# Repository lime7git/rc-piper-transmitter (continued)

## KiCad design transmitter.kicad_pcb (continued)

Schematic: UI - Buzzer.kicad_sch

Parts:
BZ1: Buzzer; Buzzer_TDK_PS1240P02BT_D12.2mm_H6.5mm
D2: 1N5819WS; D_SOD-323
JP7: SolderJumper_3_Bridged12; SolderJumper-3_P2.0mm_Open_TrianglePad1.0x1.5mm_NumberLabels
Q4: AO3400A; SOT-23
R75: 330Ω; R_0402_1005Metric
R76: 47kΩ; R_0402_1005Metric

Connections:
+3.3V: JP7.3 (B); also elsewhere on the board
+5V: JP7.1 (A); also elsewhere on the board
/Project Architecture/MCU - IO/BUZZER: R75.1; also elsewhere on the board
GND: Q4.2 (S), R76.2; also elsewhere on the board
unnamed: BZ1.1 (+), D2.1 (K), JP7.2 (C)
unnamed: BZ1.2 (-), D2.2 (A), Q4.3 (D)
unnamed: Q4.1 (G), R75.2, R76.1

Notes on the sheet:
[${#}] ${TITLE}
Incremental rotary encoder with switch

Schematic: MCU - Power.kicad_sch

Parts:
C55, C56, C57, C58, C59, C60, C61, C62, C63, C64, C65, C69, C70, C74, C75: 100nF; C_0402_1005Metric
C66, C67, C68: 1uF; C_0603_1608Metric
C71: 4.7uF; C_0805_2012Metric
C72, C73: 2.2uF; C_1206_3216Metric
J3: B2B-PH-K-S; JST_PH_B2B-PH-K_1x02_P2.00mm_Vertical; not fitted
JP3: NO; SolderJumper-2_P1.3mm_Open_TrianglePad1.0x1.5mm
JP5, JP6: NC; SolderJumper-2_P1.3mm_Open_TrianglePad1.0x1.5mm
R61, R68, R95: 0Ω; R_0402_1005Metric
U1: STM32H743ZIT6TR; LQFP-144_1_STM

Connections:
+3.3V: C55.1, C56.1, C57.1, C58.1, C59.1, C60.1, C61.1, C62.1, C63.1, C64.1, C65.1, C71.1, C74.1, JP5.2 (B), JP6.1 (A), R61.1, U1.17 (VDD), U1.30 (VDD), U1.39 (VDD), U1.52 (VDD), U1.62 (VDD), U1.72 (VDD), U1.84 (VDD), U1.108 (VDD), U1.121 (VDD), U1.131 (VDD), U1.144 (VDD); also elsewhere on the board
GND: C55.2, C56.2, C57.2, C58.2, C59.2, C60.2, C61.2, C62.2, C63.2, C64.2, C65.2, C66.2, C71.2, C72.2, C73.2, C74.2, C75.2, J3.2, R95.2, U1.16 (VSS), U1.38 (VSS), U1.51 (VSS), U1.61 (VSS), U1.83 (VSS), U1.94 (VSS), U1.107 (VSS), U1.120 (VSS), U1.130 (VSS); also elsewhere on the board
GNDA: C67.2, C68.2, C69.2, C70.2, R95.1, U1.31 (VSSA)
unnamed: J3.1, JP3.1 (A)
unnamed: JP5.1 (A), U1.95 (VDD33USB)
VBAT: C66.1, JP3.2 (B), JP6.2 (B), U1.6 (VBAT)
VCAP: C72.1, C73.1, U1.71 (VCAP), U1.106 (VCAP)
VDDA: C68.1, C70.1, C75.1, R61.2, R68.2, U1.33 (VDDA)
VREF: C67.1, C69.1, R68.1, U1.32 (VREF+)

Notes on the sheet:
VBAT power domain
Analog decoupling
VCAP decoupling
[${#}] ${TITLE}
Microcontroller power decoupling
Microcontroller power
LAYOUT NOTE: Place each capacitor close to the relevant pin.

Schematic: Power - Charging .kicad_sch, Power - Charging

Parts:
C37, C39: 4.7uF; C_0805_2012Metric
C38, C41: 100nF; C_0402_1005Metric
C42: 10uF; C_0805_2012Metric
JP9, JP10: NO; SolderJumper-2_P1.3mm_Open_TrianglePad1.0x1.5mm
R47, R48: 10kΩ; R_0402_1005Metric
R49: 300kΩ; R_0603_1608Metric
R50: 0Ω; R_0402_1005Metric; not fitted
R96, R97: 0Ω; R_0402_1005Metric
U3: MP2667GG-0000-Z; QFN-10_2MMx2MM_MNP-L

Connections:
+3.3V: R49.1; also elsewhere on the board
+BATT: C42.1, JP10.1 (A), U3.8 (BATT), U3.9 (BATT); also elsewhere on the board
/Project Architecture/Auxiliary/I2C3_SCL: U3.6 (SCL); also elsewhere on the board
/Project Architecture/Auxiliary/I2C3_SDA: U3.7 (SDA); also elsewhere on the board
/Project Architecture/MCU - IO/CHARGER_INT: R49.2, U3.3 (INT); also elsewhere on the board
/Project Architecture/Power - Battery/NTC_BATT: R50.1; also elsewhere on the board
GND: C37.2, C38.2, C39.2, C41.2, C42.2, R47.2, U3.5 (GND); also elsewhere on the board
unnamed: R97.2, U3.1 (IN)
unnamed: R47.1, R48.2, R50.2, U3.2 (NTC)
unnamed: R96.1, U3.10 (SYS)
unnamed: C38.1, U3.4 (VDD)
VBUS: C37.1, JP9.1 (A), R48.1, R97.1; also elsewhere on the board
VSYS: C39.1, C41.1, JP9.2 (B), JP10.2 (B), R96.2; also elsewhere on the board

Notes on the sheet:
[${#}] ${TITLE}
Li-pol single-cell battery charger with Ppower path managment
DESIGN NOTE: Check for I2C addresses collisions

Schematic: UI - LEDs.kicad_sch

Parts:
D4: RED; LED_0603_1608Metric
D5: WHITE; LED_0603_1608Metric
R77, R78: 1kΩ; R_0402_1005Metric

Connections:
+3.3V: R77.1; also elsewhere on the board
/Project Architecture/MCU - IO/LED: D4.1 (K), D5.2 (A); also elsewhere on the board
GND: R78.1; also elsewhere on the board
unnamed: D4.2 (A), R77.2
unnamed: D5.1 (K), R78.2

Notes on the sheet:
LEDs
[${#}] ${TITLE}

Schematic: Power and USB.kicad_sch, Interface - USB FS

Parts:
C40: 10uF; C_0805_2012Metric
C43: 100nF; C_0402_1005Metric
IC4: USBLC6-2SC6; SOT95P280X145-6N; Manufacturer_Part_Number USBLC6-2SC6
J6: USB4085-GF-A; GCT_USB4085-GF-A_REVB
R51, R52: 5.1kΩ; R_0402_1005Metric

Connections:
/Project Architecture/Interface - USB FS/DN: IC4.1 (I/O1_1), J6.A7 (D-), J6.B7 (D-)
/Project Architecture/Interface - USB FS/DP: IC4.3 (I/O2_1), J6.A6 (D+), J6.B6 (D+)
/Project Architecture/Interface - USB FS/USB_OTG_FS_DN: IC4.6 (I/O1_2); also elsewhere on the board
/Project Architecture/Interface - USB FS/USB_OTG_FS_DP: IC4.4 (I/O2_2); also elsewhere on the board
GND: C40.2, C43.2, IC4.2 (GND), J6.A1 (GND), J6.A12 (GND), J6.B1 (GND), J6.B12 (GND), J6.S1 (SHIELD), R51.2, R52.2; also elsewhere on the board
unnamed: J6.A5 (CC1), R52.1
unnamed: J6.B5 (CC2), R51.1
VBUS: C40.1, C43.1, IC4.5 (VBUS), J6.A4 (VBUS), J6.A9 (VBUS), J6.B4 (VBUS), J6.B9 (VBUS); also elsewhere on the board

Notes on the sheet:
USB C
[${#}] ${TITLE}

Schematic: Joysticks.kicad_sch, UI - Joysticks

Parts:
C23, C24, C25, C26: 100nF; C_0402_1005Metric
R16, R17, R18, R19: 0Ω; R_0402_1005Metric
RV1: LeftX; JST_PH_B3B-PH-K_1x03_P2.00mm_Vertical
RV2: LeftY; JST_PH_B3B-PH-K_1x03_P2.00mm_Vertical
RV3: RightX; JST_PH_B3B-PH-K_1x03_P2.00mm_Vertical
RV4: RightY; JST_PH_B3B-PH-K_1x03_P2.00mm_Vertical

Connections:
+3.3V: RV1.1, RV2.1, RV3.1, RV4.1; also elsewhere on the board
/Project Architecture/MCU - IO/ADC1_INP4: C23.1, R16.1; also elsewhere on the board
/Project Architecture/MCU - IO/ADC1_INP7: C24.1, R17.1; also elsewhere on the board
/Project Architecture/MCU - IO/ADC1_INP8: C25.1, R18.1; also elsewhere on the board
/Project Architecture/MCU - IO/ADC1_INP16: C26.1, R19.1; also elsewhere on the board
/Project Architecture/UI - Joysticks/LX: R16.2, RV1.2
/Project Architecture/UI - Joysticks/LY: R17.2, RV2.2
/Project Architecture/UI - Joysticks/RX: R18.2, RV3.2
/Project Architecture/UI - Joysticks/RY: R19.2, RV4.2
GND: C23.2, C24.2, C25.2, C26.2, RV1.3, RV2.3, RV3.3, RV4.3; also elsewhere on the board

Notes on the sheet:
Right axis - 5kOhm potentiometers x2
DESIGN NOTE: Each axis input is connected via JST PHR 3pin header. 1 - 3.3V 2 - INPUT 3 - GND
[${#}] ${TITLE}

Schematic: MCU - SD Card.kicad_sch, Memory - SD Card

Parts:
CARD1: TF-SMD_TF-PUSH; Manufacturer Part TF PUSH
R40, R41, R42, R43, R44, R46: 47kΩ; R_0402_1005Metric
R45: 0Ω; R_0402_1005Metric

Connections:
+3.3V: CARD1.4 (VDD), R40.1, R41.1, R42.1, R43.1, R44.1, R46.1; also elsewhere on the board
/Project Architecture/MCU - IO/CD: R45.1; also elsewhere on the board
/Project Architecture/MCU - IO/SDMMC2_CK: CARD1.5 (CLK); also elsewhere on the board
/Project Architecture/MCU - IO/SDMMC2_CMD: CARD1.3 (CMD), R44.2; also elsewhere on the board
/Project Architecture/MCU - IO/SDMMC2_D0: CARD1.7 (DAT0), R43.2; also elsewhere on the board
/Project Architecture/MCU - IO/SDMMC2_D1: CARD1.8 (DAT1), R42.2; also elsewhere on the board
/Project Architecture/MCU - IO/SDMMC2_D2: CARD1.1 (DAT2), R41.2; also elsewhere on the board
/Project Architecture/MCU - IO/SDMMC2_D3: CARD1.2 (CD/DAT3), R40.2; also elsewhere on the board
GND: CARD1.6 (VSS); also elsewhere on the board
unnamed: CARD1.CD, R45.2, R46.2

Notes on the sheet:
[${#}] ${TITLE}
SD Card
DESIGN NOTE: Matched length on SDMMC2 net. [2.54mm tolerance]

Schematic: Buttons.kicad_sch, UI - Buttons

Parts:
C27, C28, C29, C30, C31, C32, C33, C34: 100nF; C_0402_1005Metric
D6, D7, D8, D9, D10, D11, D12, D13: ESD5Z5V0; D_SOD-523; not fitted
R20, R23, R25, R27, R29, R31, R33, R35: 47kΩ; R_0402_1005Metric
R21, R22, R24, R26, R28, R30, R32, R34: 5.1kΩ; R_0402_1005Metric
SW1, SW2, SW3, SW4, SW5, SW6, SW10, SW11: Button SPST SMD Tactile Switch; JST_PH_B2B-PH-K_1x02_P2.00mm_Vertical

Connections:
+3.3V: R20.1, R23.1, R25.1, R27.1, R29.1, R31.1, R33.1, R35.1; also elsewhere on the board
/Project Architecture/Auxiliary/BUTTON0: R21.1; also elsewhere on the board
/Project Architecture/Auxiliary/BUTTON1: R22.1; also elsewhere on the board
/Project Architecture/Auxiliary/BUTTON2: R24.1; also elsewhere on the board
/Project Architecture/Auxiliary/BUTTON3: R26.1; also elsewhere on the board
/Project Architecture/Auxiliary/BUTTON4: R28.1; also elsewhere on the board
/Project Architecture/Auxiliary/BUTTON5: R30.1; also elsewhere on the board
/Project Architecture/Auxiliary/BUTTON6: R32.1; also elsewhere on the board
/Project Architecture/Auxiliary/BUTTON7: R34.1; also elsewhere on the board
GND: C27.2, C28.2, C29.2, C30.2, C31.2, C32.2, C33.2, C34.2, D6.2 (A), D7.2 (A), D8.2 (A), D9.2 (A), D10.2 (A), D11.2 (A), D12.2 (A), D13.2 (A), SW1.2, SW2.2, SW3.2, SW4.2, SW5.2, SW6.2, SW10.2, SW11.2; also elsewhere on the board
unnamed: C28.1, D6.1 (K), R22.2, R23.2, SW2.1
unnamed: C29.1, D7.1 (K), R24.2, R25.2, SW3.1
unnamed: C27.1, D8.1 (K), R20.2, R21.2, SW1.1
unnamed: C30.1, D9.1 (K), R26.2, R27.2, SW4.1
unnamed: C31.1, D10.1 (K), R28.2, R29.2, SW5.1
unnamed: C32.1, D11.1 (K), R30.2, R31.2, SW6.1
unnamed: C33.1, D12.1 (K), R32.2, R33.2, SW10.1
unnamed: C34.1, D13.1 (K), R34.2, R35.2, SW11.1

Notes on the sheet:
Push button - SPST - right angle
[${#}] ${TITLE}
Push button - SPST

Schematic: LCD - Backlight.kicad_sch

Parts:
C14, C16, C17: 4.7uF; C_0805_2012Metric
C15: 100nF; C_0402_1005Metric
C18: 220nF; C_0402_1005Metric
D1: 1N5819WS; D_SOD-323
IC2: TPS61165DBVR; SOT95P280X145-6N; Mouser Part Number 595-TPS61165DBVR
L1: 1.33A 10uH; IND_VLS3012HBX-100M
L2, L3: GZ2012D601TF; L_0805_2012Metric
R9: 0Ω; R_0402_1005Metric
R10: 10kΩ; R_0402_1005Metric
R11: 1Ω; R_0603_1608Metric
R12: 2Ω; R_0603_1608Metric

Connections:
/Project Architecture/LCD - Backlight/BACKLIGHT_PWM: R9.1; also elsewhere on the board
/Project Architecture/LCD - Backlight/BLHV: D1.2 (A), IC2.3 (SW), L1.2
/Project Architecture/LCD - Backlight/CTRL: IC2.2 (CTRL), R9.2, R10.2
/Project Architecture/LCD - Backlight/LCD_BACKLIGHT_V+: C16.1, C17.1, D1.1 (K); also elsewhere on the board
/Project Architecture/LCD - Backlight/LCD_BACKLIGHT_V-: IC2.6 (FB), R11.1; also elsewhere on the board
BLGND: C14.2, C15.2, C16.2, C17.2, C18.2, IC2.4 (GND), L3.2, R12.2
BLVDD: C14.1, C15.1, IC2.1 (VIN), L1.1, L2.2
GND: L3.1, R10.1; also elsewhere on the board
unnamed: C18.1, IC2.5 (COMP)
unnamed: R11.2, R12.1
VSYS_SW: L2.1; also elsewhere on the board

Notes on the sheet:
PWM brightness dimming signal
LAYOUT NOTE: Keep input capacitors as close to VIN and GND as possible!
LAYOUT NOTE: Keep the SW area as close and as small as possible!
[${#}] ${TITLE}
LCD backlight LED driver

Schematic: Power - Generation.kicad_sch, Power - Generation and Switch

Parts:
C44, C45: 10uF; C_0805_2012Metric
C46: 1uF; C_0603_1608Metric
C47, C53, C54: 100nF; C_0402_1005Metric
C48: 100pF; C_0603_1608Metric
C49, C50: 22uF; C_0805_2012Metric
C51, C52: 10uF 16V; CP_EIA-3216-18_Kemet-A
D3: 1N5819WS; D_SOD-323
JP1: NO; SolderJumper-2_P1.3mm_Open_TrianglePad1.0x1.5mm
L4: 1.8A 1uH; L_Cenker_CKCS4018
Q1, Q2: AO3400A; SOT-23
Q3: SI2301CDS-T1-GE3; SOT-23
R53, R60, R62, R66: 100kΩ; R_0402_1005Metric
R54, R58, R59: 0Ω; R_0402_1005Metric
R55: 0Ω; R_0402_1005Metric; not fitted
R56: 47kΩ; R_0402_1005Metric
R57: 10kΩ; R_0402_1005Metric
R63: 330Ω; R_0402_1005Metric
R64: 300kΩ; R_0603_1608Metric
R65: 1kΩ; R_0402_1005Metric
R67: 634kΩ; R_0402_1005Metric
SW8: Button SPST SMD Tactile Switch; SW_TS-1088-AR02016
U4: AMS1117-3.3; SOT-223-3_TabPin2
U5: TPS61252DSG; WSON-8-1EP_2x2mm_P0.5mm_EP0.9x1.6mm

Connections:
+3.3V: C52.1, C54.1, U4.2 (VO); also elsewhere on the board
+5V: C48.1, C49.1, C50.1, C51.1, C53.1, R67.1, U4.3 (VI), U5.2 (VOUT); also elsewhere on the board
/Project Architecture/MCU - IO/uC_PWR: R65.2; also elsewhere on the board
/Project Architecture/Power - Generation and Switch/VBUS_CTRL: Q2.3 (D), R58.2
/Project Architecture/Power - Generation and Switch/uC_CTRL: D3.2 (A), R62.2, R64.1, R65.1
GND: C44.2, C49.2, C50.2, C51.2, C52.2, C53.2, C54.2, Q1.2 (S), Q2.2 (S), R55.2, R56.2, R66.2, SW8.2, U4.1 (GND), U5.1 (GND), U5.9 (GND); also elsewhere on the board
unnamed: C46.1, D3.1 (K), R57.1, SW8.1
unnamed: Q1.3 (D), R54.2
unnamed: C45.2, Q1.1 (G), R64.2
unnamed: Q2.1 (G), R56.1, R63.2
unnamed: C46.2, C47.2, Q3.1 (G), R53.2, R54.1, R58.1
unnamed: R60.2, R66.1
unnamed: C48.2, R60.1, R67.2, U5.3 (FB)
unnamed: R55.1, R59.2, U5.4 (ILIM)
unnamed: L4.2, U5.7 (SW)
VBUS: R63.1; also elsewhere on the board
VSYS: C47.1, JP1.1 (A), Q3.2 (S), R53.1, R57.2; also elsewhere on the board
VSYS_SW: C44.1, C45.1, JP1.2 (B), L4.1, Q3.3 (D), R59.1, R62.1, U5.6 (EN), U5.8 (VIN); also elsewhere on the board

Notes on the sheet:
LAYOUT NOTE: Keep the SW area as close and as small as possible!
[${#}] ${TITLE}
High-side power switch (Press ON - Hold OFF)
VBUS power control
uC power control
5V to 3.3V LDO
DESIGN NOTE: Implemenation of high-side latching power switch that allows to enable power by pressing power button or by plugging USB power. Then the power can be disabled by microcontroller which is also detecting another power button events or force disabled by holding power button for several se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
VSYS (single-cell li-pol/VBUS) to 5V boost converter

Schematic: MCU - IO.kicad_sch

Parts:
U1: STM32H743ZIT6TR; LQFP-144_1_STM

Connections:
/Project Architecture/Auxiliary/DEBUG_SWCLK: U1.109 (PA14); also elsewhere on the board
/Project Architecture/Auxiliary/DEBUG_SWDIO: U1.105 (PA13); also elsewhere on the board
/Project Architecture/Auxiliary/I2C3_SCL: U1.100 (PA8); also elsewhere on the board
/Project Architecture/Auxiliary/I2C3_SDA: U1.99 (PC9); also elsewhere on the board
/Project Architecture/Auxiliary/NRST: U1.25 (NRST); also elsewhere on the board
/Project Architecture/Auxiliary/PD5: U1.119 (PD5); also elsewhere on the board
/Project Architecture/Auxiliary/PE3: U1.2 (PE3); also elsewhere on the board
/Project Architecture/Auxiliary/PG3: U1.88 (PG3); also elsewhere on the board
/Project Architecture/Auxiliary/PG9: U1.124 (PG9); also elsewhere on the board
/Project Architecture/Auxiliary/RCC_OSC32_IN: U1.8 (PC14-OSC32_IN); also elsewhere on the board
/Project Architecture/Auxiliary/RCC_OSC32_OUT: U1.9 (PC15-OSC32_OUT); also elsewhere on the board
/Project Architecture/Auxiliary/RCC_OSC_IN: U1.23 (PH0-OSC_IN); also elsewhere on the board
/Project Architecture/Auxiliary/RCC_OSC_OUT: U1.24 (PH1-OSC_OUT); also elsewhere on the board
/Project Architecture/Auxiliary/TOGGLE0: U1.135 (PB5); also elsewhere on the board
/Project Architecture/Auxiliary/TOGGLE1: U1.73 (PB12); also elsewhere on the board
/Project Architecture/Interface - RF Transmitter/RF_CE: U1.129 (PG14); also elsewhere on the board
/Project Architecture/Interface - RF Transmitter/RF_IRQ: U1.87 (PG2); also elsewhere on the board
/Project Architecture/Interface - RF Transmitter/SPI5_MISO: U1.20 (PF8); also elsewhere on the board
/Project Architecture/Interface - RF Transmitter/SPI5_MOSI: U1.21 (PF9); also elsewhere on the board
/Project Architecture/Interface - RF Transmitter/SPI5_NSS: U1.18 (PF6); also elsewhere on the board
/Project Architecture/Interface - RF Transmitter/SPI5_SCK: U1.19 (PF7); also elsewhere on the board
/Project Architecture/Interface - USB FS/USB_OTG_FS_DN: U1.103 (PA11); also elsewhere on the board
/Project Architecture/Interface - USB FS/USB_OTG_FS_DP: U1.104 (PA12); also elsewhere on the board
/Project Architecture/LCD - Backlight/BACKLIGHT_PWM: U1.137 (PB7); also elsewhere on the board
/Project Architecture/LCD - Connectors/LTDC_B0: U1.3 (PE4); also elsewhere on the board
/Project Architecture/LCD - Connectors/LTDC_B1: U1.102 (PA10); also elsewhere on the board
/Project Architecture/LCD - Connectors/LTDC_B2: U1.122 (PD6); also elsewhere on the board
/Project Architecture/LCD - Connectors/LTDC_B3: U1.126 (PG11); also elsewhere on the board
/Project Architecture/LCD - Connectors/LTDC_B4: U1.127 (PG12); also elsewhere on the board
/Project Architecture/LCD - Connectors/LTDC_B5: U1.37 (PA3); also elsewhere on the board
/Project Architecture/LCD - Connectors/LTDC_B6: U1.139 (PB8); also elsewhere on the board
/Project Architecture/LCD - Connectors/LTDC_B7: U1.140 (PB9); also elsewhere on the board
/Project Architecture/LCD - Connectors/LTDC_CLK: U1.92 (PG7); also elsewhere on the board
/Project Architecture/LCD - Connectors/LTDC_DE: U1.22 (PF10); also elsewhere on the board
/Project Architecture/LCD - Connectors/LTDC_G0: U1.4 (PE5); also elsewhere on the board
/Project Architecture/LCD - Connectors/LTDC_G1: U1.5 (PE6); also elsewhere on the board
/Project Architecture/LCD - Connectors/LTDC_G2: U1.42 (PA6); also elsewhere on the board
/Project Architecture/LCD - Connectors/LTDC_G3: U1.125 (PG10); also elsewhere on the board
/Project Architecture/LCD - Connectors/LTDC_G4: U1.69 (PB10); also elsewhere on the board
/Project Architecture/LCD - Connectors/LTDC_G5: U1.70 (PB11); also elsewhere on the board
/Project Architecture/LCD - Connectors/LTDC_G6: U1.97 (PC7); also elsewhere on the board
/Project Architecture/LCD - Connectors/LTDC_G7: U1.117 (PD3); also elsewhere on the board
/Project Architecture/LCD - Connectors/LTDC_HSYNC: U1.96 (PC6); also elsewhere on the board
/Project Architecture/LCD - Connectors/LTDC_R0: U1.128 (PG13); also elsewhere on the board
/Project Architecture/LCD - Connectors/LTDC_R1: U1.36 (PA2); also elsewhere on the board
/Project Architecture/LCD - Connectors/LTDC_R2: U1.111 (PC10); also elsewhere on the board
/Project Architecture/LCD - Connectors/LTDC_R3: U1.46 (PB0); also elsewhere on the board
/Project Architecture/LCD - Connectors/LTDC_R4: U1.41 (PA5); also elsewhere on the board
/Project Architecture/LCD - Connectors/LTDC_R5: U1.101 (PA9); also elsewhere on the board
/Project Architecture/LCD - Connectors/LTDC_R6: U1.47 (PB1); also elsewhere on the board
/Project Architecture/LCD - Connectors/LTDC_R7: U1.91 (PG6); also elsewhere on the board
/Project Architecture/LCD - Connectors/LTDC_VSYNC: U1.40 (PA4); also elsewhere on the board
/Project Architecture/MCU - IO/ADC1_INP4: U1.44 (PC4); also elsewhere on the board
/Project Architecture/MCU - IO/ADC1_INP7: U1.43 (PA7); also elsewhere on the board
/Project Architecture/MCU - IO/ADC1_INP8: U1.45 (PC5); also elsewhere on the board
/Project Architecture/MCU - IO/ADC1_INP16: U1.34 (PA0); also elsewhere on the board
/Project Architecture/MCU - IO/BOOT0: U1.138 (BOOT0); also elsewhere on the board
/Project Architecture/MCU - IO/BUZZER: U1.7 (PC13); also elsewhere on the board
/Project Architecture/MCU - IO/CD: U1.74 (PB13); also elsewhere on the board
/Project Architecture/MCU - IO/CHARGER_INT: U1.98 (PC8); also elsewhere on the board
/Project Architecture/MCU - IO/ENC_BUTTON: U1.116 (PD2); also elsewhere on the board
/Project Architecture/MCU - IO/EXPANDER_INT: U1.118 (PD4); also elsewhere on the board
/Project Architecture/MCU - IO/FMC_A0: U1.10 (PF0); also elsewhere on the board
/Project Architecture/MCU - IO/FMC_A1: U1.11 (PF1); also elsewhere on the board
/Project Architecture/MCU - IO/FMC_A2: U1.12 (PF2); also elsewhere on the board
/Project Architecture/MCU - IO/FMC_A3: U1.13 (PF3); also elsewhere on the board
/Project Architecture/MCU - IO/FMC_A4: U1.14 (PF4); also elsewhere on the board
/Project Architecture/MCU - IO/FMC_A5: U1.15 (PF5); also elsewhere on the board
/Project Architecture/MCU - IO/FMC_A6: U1.50 (PF12); also elsewhere on the board
/Project Architecture/MCU - IO/FMC_A7: U1.53 (PF13); also elsewhere on the board
/Project Architecture/MCU - IO/FMC_A8: U1.54 (PF14); also elsewhere on the board
/Project Architecture/MCU - IO/FMC_A9: U1.55 (PF15); also elsewhere on the board
/Project Architecture/MCU - IO/FMC_A10: U1.56 (PG0); also elsewhere on the board
/Project Architecture/MCU - IO/FMC_A11: U1.57 (PG1); also elsewhere on the board
/Project Architecture/MCU - IO/FMC_BA0: U1.89 (PG4); also elsewhere on the board
/Project Architecture/MCU - IO/FMC_BA1: U1.90 (PG5); also elsewhere on the board
/Project Architecture/MCU - IO/FMC_D0: U1.85 (PD14); also elsewhere on the board
/Project Architecture/MCU - IO/FMC_D1: U1.86 (PD15); also elsewhere on the board
/Project Architecture/MCU - IO/FMC_D2: U1.114 (PD0); also elsewhere on the board
/Project Architecture/MCU - IO/FMC_D3: U1.115 (PD1); also elsewhere on the board
/Project Architecture/MCU - IO/FMC_D4: U1.58 (PE7); also elsewhere on the board
/Project Architecture/MCU - IO/FMC_D5: U1.59 (PE8); also elsewhere on the board
/Project Architecture/MCU - IO/FMC_D6: U1.60 (PE9); also elsewhere on the board
/Project Architecture/MCU - IO/FMC_D7: U1.63 (PE10); also elsewhere on the board
/Project Architecture/MCU - IO/FMC_D8: U1.64 (PE11); also elsewhere on the board
/Project Architecture/MCU - IO/FMC_D9: U1.65 (PE12); also elsewhere on the board
/Project Architecture/MCU - IO/FMC_D10: U1.66 (PE13); also elsewhere on the board
/Project Architecture/MCU - IO/FMC_D11: U1.67 (PE14); also elsewhere on the board
/Project Architecture/MCU - IO/FMC_D12: U1.68 (PE15); also elsewhere on the board
/Project Architecture/MCU - IO/FMC_D13: U1.77 (PD8); also elsewhere on the board
/Project Architecture/MCU - IO/FMC_D14: U1.78 (PD9); also elsewhere on the board
/Project Architecture/MCU - IO/FMC_D15: U1.79 (PD10); also elsewhere on the board
/Project Architecture/MCU - IO/FMC_NBL0: U1.141 (PE0); also elsewhere on the board
/Project Architecture/MCU - IO/FMC_NBL1: U1.142 (PE1); also elsewhere on the board
/Project Architecture/MCU - IO/FMC_SDCKE0: U1.29 (PC3_C); also elsewhere on the board
/Project Architecture/MCU - IO/FMC_SDCLK: U1.93 (PG8); also elsewhere on the board
/Project Architecture/MCU - IO/FMC_SDNCAS: U1.132 (PG15); also elsewhere on the board
/Project Architecture/MCU - IO/FMC_SDNE0: U1.28 (PC2_C); also elsewhere on the board
/Project Architecture/MCU - IO/FMC_SDNRAS: U1.49 (PF11); also elsewhere on the board
/Project Architecture/MCU - IO/FMC_SDNWE: U1.26 (PC0); also elsewhere on the board
/Project Architecture/MCU - IO/LED: U1.113 (PC12); also elsewhere on the board
/Project Architecture/MCU - IO/PDR_ON: U1.143 (PDR_ON); also elsewhere on the board
/Project Architecture/MCU - IO/QUADSPI_BK1_IO0: U1.80 (PD11); also elsewhere on the board
/Project Architecture/MCU - IO/QUADSPI_BK1_IO1: U1.81 (PD12); also elsewhere on the board
/Project Architecture/MCU - IO/QUADSPI_BK1_IO2: U1.1 (PE2); also elsewhere on the board
/Project Architecture/MCU - IO/QUADSPI_BK1_IO3: U1.82 (PD13); also elsewhere on the board
/Project Architecture/MCU - IO/QUADSPI_BK1_NCS: U1.136 (PB6); also elsewhere on the board
/Project Architecture/MCU - IO/QUADSPI_CLK: U1.48 (PB2); also elsewhere on the board
/Project Architecture/MCU - IO/SDMMC2_CK: U1.27 (PC1); also elsewhere on the board
/Project Architecture/MCU - IO/SDMMC2_CMD: U1.123 (PD7); also elsewhere on the board
/Project Architecture/MCU - IO/SDMMC2_D0: U1.75 (PB14); also elsewhere on the board
/Project Architecture/MCU - IO/SDMMC2_D1: U1.76 (PB15); also elsewhere on the board
/Project Architecture/MCU - IO/SDMMC2_D2: U1.133 (PB3); also elsewhere on the board
/Project Architecture/MCU - IO/SDMMC2_D3: U1.134 (PB4); also elsewhere on the board
/Project Architecture/MCU - IO/TIM2_CH1: U1.110 (PA15); also elsewhere on the board
/Project Architecture/MCU - IO/TIM2_CH2: U1.35 (PA1); also elsewhere on the board
/Project Architecture/MCU - IO/uC_PWR: U1.112 (PC11); also elsewhere on the board

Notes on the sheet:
Flexible I/O worked examples
References:
Flexible I/O source configuration
[${#}] ${TITLE}

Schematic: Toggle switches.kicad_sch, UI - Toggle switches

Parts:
C35, C36: 100nF; C_0402_1005Metric
D14, D15: ESD5Z5V0; D_SOD-523; not fitted
R36, R38: 5.1kΩ; R_0402_1005Metric
R37, R39: 47kΩ; R_0402_1005Metric
SW7: SW_SPDT_MSM; JST_PH_B3B-PH-K_1x03_P2.00mm_Vertical

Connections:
+3.3V: R37.1, R39.1; also elsewhere on the board
/Project Architecture/Auxiliary/TOGGLE0: R36.1; also elsewhere on the board
/Project Architecture/Auxiliary/TOGGLE1: R38.1; also elsewhere on the board
GND: C35.2, C36.2, D14.2 (A), D15.2 (A), SW7.2 (3); also elsewhere on the board
unnamed: C36.1, D14.1 (K), R38.2, R39.2, SW7.1
unnamed: C35.1, D15.1 (K), R36.2, R37.2, SW7.3 (4)

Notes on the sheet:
[${#}] ${TITLE}
Toggle switch - 3pos

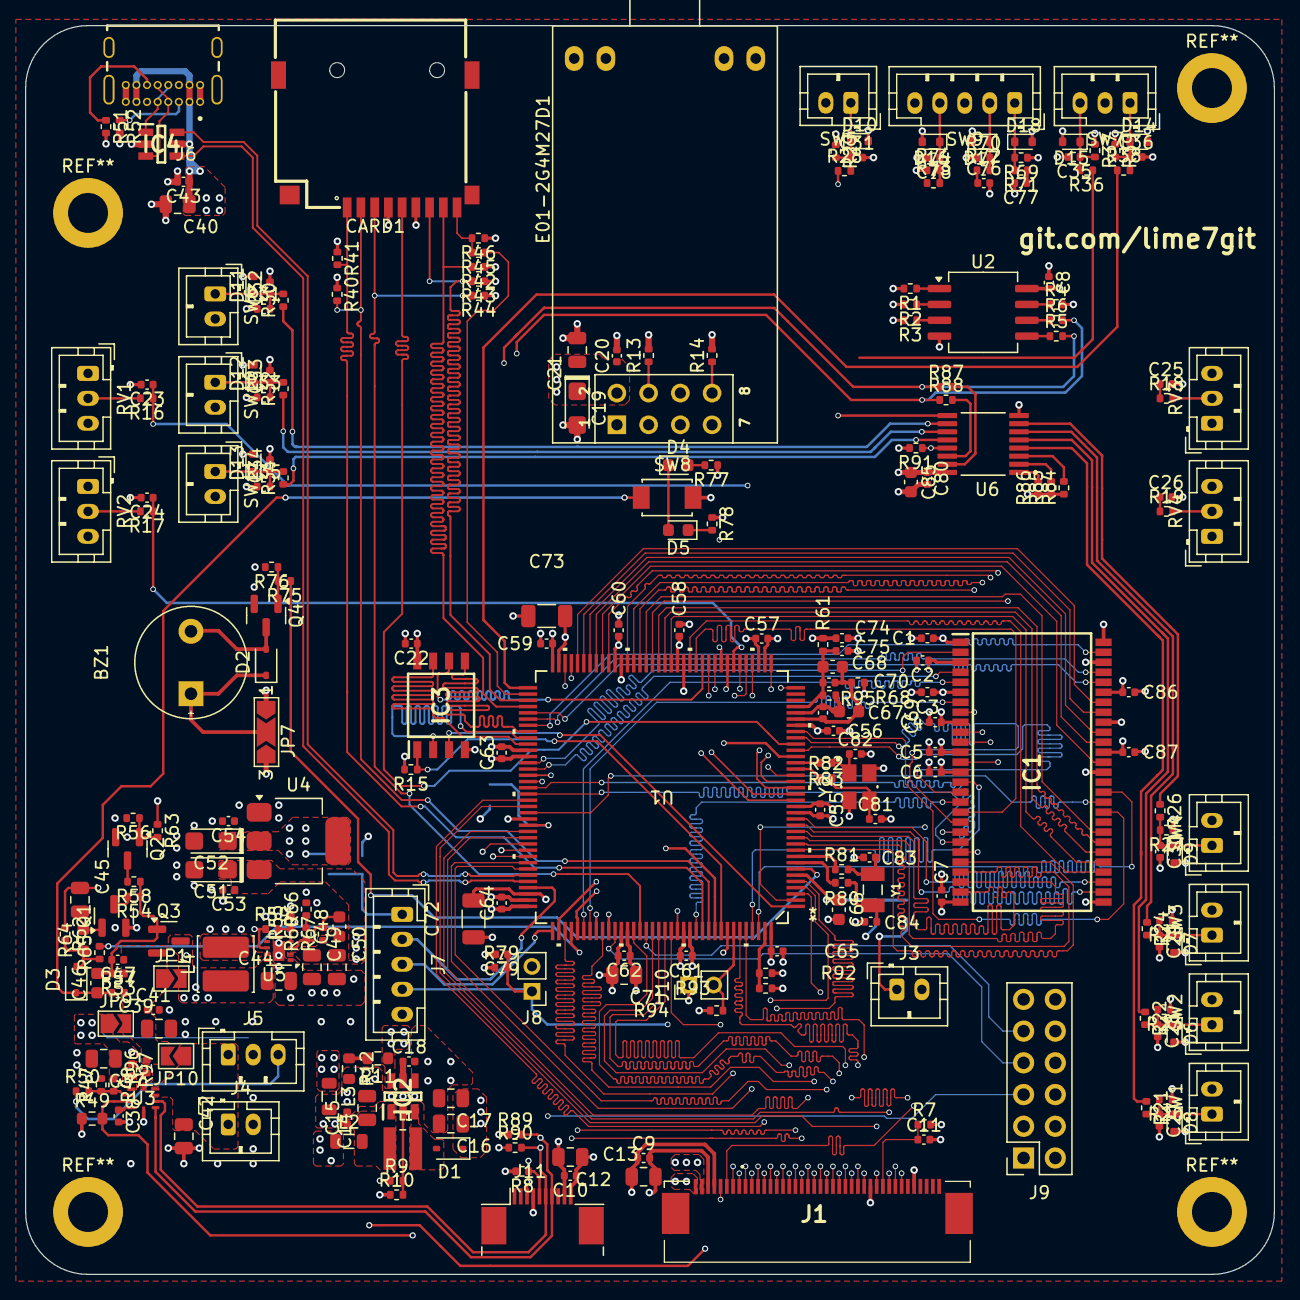
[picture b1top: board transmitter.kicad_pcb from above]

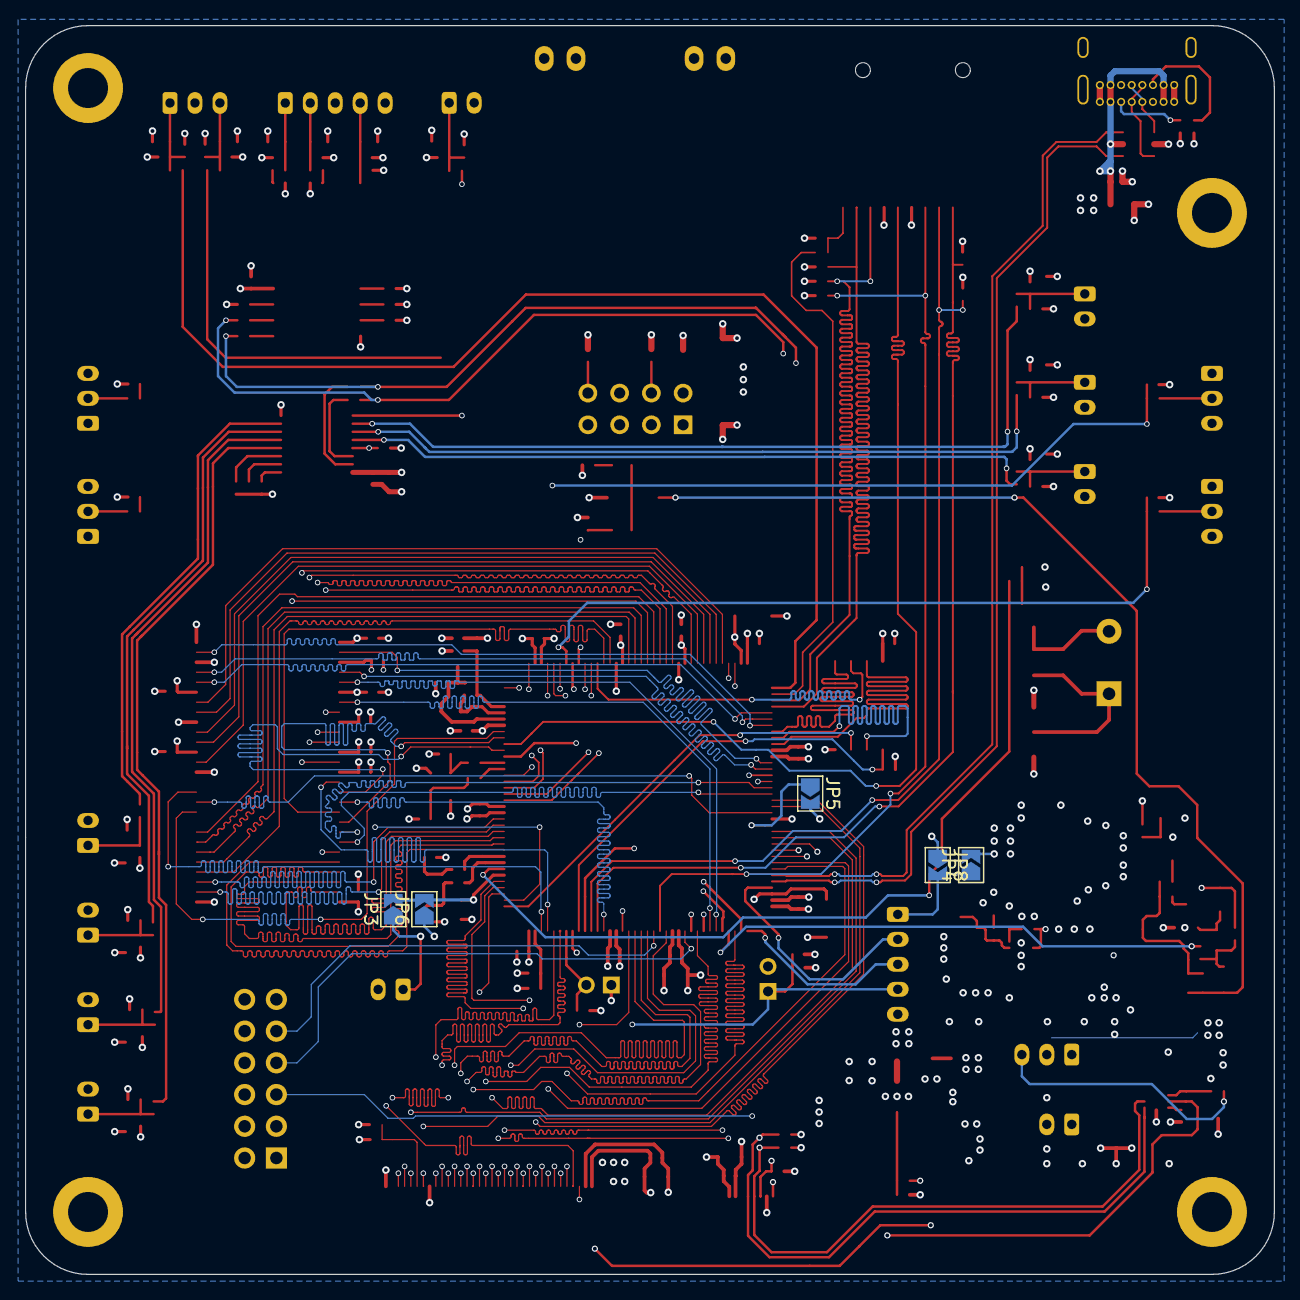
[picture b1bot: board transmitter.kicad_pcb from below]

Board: 6 copper layers, 100.0 x 100.0 mm, 259 parts (5 on the bottom side), 208 nets.

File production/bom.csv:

Designator,Footprint,Quantity,Value,LCSC Part #
BZ1,Buzzer_TDK_PS1240P02BT_D12.2mm_H6.5mm,1,Buzzer,
"C1, C10, C11, C15, C2, C20, C22, C23, C24, C25, C26, C27, C28, C29, C3, C30, C31, C32, C33, C34, C35, C36, C38, C4, C41, C43, C47, C5, C53, C54, C55, C56, C57, C58, C59, C6, C60, C61, C62, C63, C64, C65, C69, C7, C70, C74, C75, C76, C77, C78, C79, C80, C86, C87, C9",0402,55,100nF,
"C12, C13, C14, C16, C17, C21, C37, C39, C71",0805,9,4.7uF,
C18,0402,1,220nF,
"C19, C51, C52",CP_EIA-3216-18_Kemet-A,3,10uF 16V,
"C40, C42, C44, C45",0805,4,10uF,
"C46, C66, C67, C68, C85",0603,5,1uF,
C48,0603,1,100pF,
"C49, C50",0805,2,22uF,
"C72, C73",1206,2,2.2uF,
CARD1,TF-SMD_TF-PUSH,1,~,
"D1, D2, D3",D_SOD-323,3,1N5819WS,
D4,0603,1,RED,
D5,0603,1,WHITE,
E01-2G4M27D1,PE01-ML01DP5,1,DS1023-2*4SF11,
IC1,SOP80P1176X120-54N,1,W9864G6KH-6,
IC2,SOT95P280X145-6N,1,TPS61165DBVR,
IC3,SOIC127P790X216-8L,1,MT25QL128ABA1ESE-0SIT,
IC4,SOT95P280X145-6N,1,USBLC6-2SC6,
J1,AFC07-S40ECA-00,1,AFC07-S40ECA-00,
J11,AFC07S10ECC00,1,AFC07-S10FCC-00,
J4,JST_PH_B2B-PH-K_1x02_P2.00mm_Vertical,1,B2B-PH-K-S,
J6,GCT_USB4085-GF-A_REVB,1,USB4085-GF-A,
J7,JST_PH_B5B-PH-K_1x05_P2.00mm_Vertical,1,Conn_01x05,
"JP1, JP10, JP3, JP8, JP9",SolderJumper-2_P1.3mm_Open_TrianglePad1.0x1.5mm,5,NO,
"JP4, JP5, JP6",SolderJumper-2_P1.3mm_Open_TrianglePad1.0x1.5mm,3,NC,
L1,IND_VLS3012HBX-100M,1,1.33A 10uH,
"L2, L3",0805,2,GZ2012D601TF,
L4,L_Cenker_CKCS4018,1,1.8A 1uH,
"Q1, Q2, Q4",SOT-23,3,AO3400A,
Q3,SOT-23,1,SI2301CDS-T1-GE3,
"R10, R13, R14, R15, R47, R48, R57, R69, R7, R70, R71, R72, R79, R8, R84, R85, R86, R91, R93, R94",0402,20,10kΩ,
R11,0603,1,1Ω,
R12,0603,1,2Ω,
"R16, R17, R18, R19, R45, R54, R58, R59, R61, R68, R80, R81, R82, R83, R87, R88, R9, R95, R96, R97",0402,20,0Ω,
"R20, R23, R25, R27, R29, R31, R33, R35, R37, R39, R40, R41, R42, R43, R44, R46, R56, R74, R76",0402,19,47kΩ,
"R21, R22, R24, R26, R28, R30, R32, R34, R36, R38, R51, R52, R73, R89, R90",0402,15,5.1kΩ,
"R49, R64",0603,2,300kΩ,
"R53, R60, R62, R66",0402,4,100kΩ,
"R63, R75",0402,2,330Ω,
"R65, R77, R78",0402,3,1kΩ,
R67,0402,1,634kΩ,
RV1,JST_PH_B3B-PH-K_1x03_P2.00mm_Vertical,1,LeftX,
RV2,JST_PH_B3B-PH-K_1x03_P2.00mm_Vertical,1,LeftY,
RV3,JST_PH_B3B-PH-K_1x03_P2.00mm_Vertical,1,RightX,
RV4,JST_PH_B3B-PH-K_1x03_P2.00mm_Vertical,1,RightY,
"S1, S2",SKRTLAE010,2,SKRTLAE010,
"SW1, SW2, SW3, SW4, SW5, SW6, SW8",SW_TS-1088-AR02016,7,Button SPST SMD Tactile Switch,
SW7,JST_PH_B3B-PH-K_1x03_P2.00mm_Vertical,1,SW_SPDT_MSM,
SW9,JST_PH_B5B-PH-K_1x05_P2.00mm_Vertical,1,RotaryEncoder_Switch,
U1,LQFP-144_1_STM,1,STM32H743ZIT6TR,
U3,QFN-10_2MMx2MM_MNP-L,1,MP2667GG-0000-Z,
U4,SOT-223-3_TabPin2,1,AMS1117-3.3,
U5,WSON-8-1EP_2x2mm_P0.5mm_EP0.9x1.6mm,1,TPS61252DSG,
U6,SOP65P640X120-16N,1,PCA9554APW,
Y1,Q13FC13500004-32.768KHZ-4-T,1,32.768KHZ,
Y2,X322525MOB4SI 25MHz,1,X322525MOB4SI-25MHz,

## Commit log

2025-07-12 update project libraries and add connector images
    Create sym-lib-table
2025-07-12 added schematics and pcb, configure project
2025-07-12 update libraries
2025-07-12 added lcd backlight schematic
2025-07-12 fix ffc footprint
2025-07-13 added RF ransceiver
2025-07-13 qspi flash
2025-07-14 added joystick inputs
2025-07-14 added buttons schematic
2025-07-14 3 pos toggle switch input
2025-07-14 sd card image add
2025-07-17 added sd card schematic and refactor page numbers and general tab
2025-07-28 added li-pol input, start creating charging circuit
2025-07-29 small changes
2025-07-30 change page numers
2025-07-30 added emi for usb port and usb schematic
2025-07-30 usb new footprint
2025-07-30 added pchannel mosfet and boost converter tps613222
2025-07-30 added tps61252 boost converter and started working on power - generatio and on/off control schematic
2025-07-31 added power switch, 5V and 3V3 power generation
2025-07-31 charging int and i2c
2025-07-31 Create power-switch-falstad-circuit.txt
    simulation for power switch schematic
2025-08-01 added power for mcu
2025-08-01 change some solder bridges from no to nc
2025-08-01 added encoder input connector
2025-08-03 added buzzer schematic
2025-08-03 added red and white led
2025-08-03 led schematic
2025-08-23 added auxiliary schematic, problem with kicad - cannot modify project settings
2025-09-01 added auxialry - swd connector and NRST pin circuit
2025-09-01 added 25MHz and 32.768KHz oscillators
2025-09-01 added 6.8pf 0402 capacitor
2025-09-01 added schematic for crystal oscillators
2025-09-03 added signals from all sheets to mcu-io
2025-09-03 added gpio expander, uc pinout, unused gpio connector, i2c pullup, delete unused files
2025-09-10 added 2pin 2.54 male header and connect boot0, pdr_on signals
2025-09-10 added power jumper to bypass charger
2025-09-10 added jumper to connect vbat directly to vsys
2025-09-10 update project structure and import to pcb
2025-09-10 change 32.768kHz footrpint
2025-09-11 example new layout
2025-09-11 change to 6layer
2025-09-22 added some small changes on schematics - added some decoupling caps and test production files
2025-09-22 very very prototype layout + routing sdram
2025-09-24 slightly new layout and sdram routing
2025-09-27 wstepny layout i routing wokol procka i sdram, do zrobienia length tuning ramu
    - procek / decoupling
    - rcc 32khz 25mhz
    - sdram
2025-09-27 change stackup dimensions
    according to https://jlcpcb.com/6-layer-pcb
2025-09-27 trace length matching sdram, almost done 80%
2025-09-27 sdram routed and length matching done
2025-09-27 starting layout of lcd connector
2025-09-28 duzo zmian, layout przetwornic i zasilania, wstepny routing sd card impedance control, usb differential impedance control
2025-09-30 routed spi and signals to nrf24 rf module
2025-09-30 mala zmiana niektorych polaczen i layoutu, podlaczenie usb, rozpoczecie routowania sekcji zasilania - charger ic
2025-10-02 routing ladowania i obwodu przełączajacego zasilanie + vbus na in3
2025-10-02 routing zasilania caly czas + polygony masy, lekkie zmienienie layoutu - chyba dążenie do zmniejszenia wymiarow plytki - moze 100x100mm?
2025-10-08 routing zasilaczy + layout przetwornicy backlight, zmiana gniazd lcd connector - obrocenie top/bottom contacts, zmniejszenie gabarytow plytki - 100 height, przygotowanie pod 100width - max 100x100
2025-10-09 update footprints, 3d models and layout
2025-10-09 routing backlight converter
2025-10-09 backlight converter routed
2025-10-09 lcd connector routing
2025-10-10 all lcd signals routed - consider length matching?
2025-10-10 initial ltdc length matching
2025-10-10 layout fixing - hard to fit lengtmatching - a little bit spread out
2025-10-11 layout power + lcd connectors before lengthmatching again
2025-10-11 finish layout power section
2025-10-11 lcd connector length matching done 65.5mm
2025-10-12 qspi layout, length matching, sdcard lengthmatching, change some footprints, prototype production generation
2025-10-13 change buttons footprints to 2pin 2.0mm connectors
2025-10-13 added tvs diodes to protect inputs + final component placement
2025-10-14 buttons, connector inputs layout and routing
2025-10-14 end of routing
2025-10-17 clean schematics, started adding testpoints, remove designators, add some silkscreen top, added teardrops, round corners usb diff pair
2025-10-20 upgrade mcu schematic started adding testpoints
2025-10-22 added gas guage IC for monitoring battery
2025-10-22 added into pcb , layout and routing
2025-10-23 change the rf trasceiver and improve grounding near vias close to lcd connector
2025-10-24 added fiducal markers, mounting holes, testpoints
2025-10-25 some visual changes, color of nets etc
2025-10-25 test points, colors, drc
2025-10-25 clearing some drc errors
2025-10-26 fixing drc, generation production files test
2025-10-26 designator chagnes and cleanup silkscreen
2025-10-27 silkscreen
